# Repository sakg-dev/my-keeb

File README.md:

## My keeb
My first self made mechanical keyboard:
A 60% alice type tactile keyboard, properties:
- Hot swappable: through kailh socker
- 61 keys: no dedicated arrow keys or f keys
- Includes rgb light: individual rgbs

### Imgs:
- Schematics And PCB:
    - Schematics:
        - Main: 
        - Switches: 
        - RGBs: 
    - PCB:
        - F.Cu: 
        - B.Cu: 
        - F.Cu: 
- Onshape:
    - Final:
        - 
        - 

## Development And Output Files
- Layout: [layout_v1.json](/layout/layout_v1.json)
- Schematics and PCB: [kicad/](/kicad/)
- Gerber file: [gerber.zip](/gerber.zip)
- Onshape exports: [onshape_exports/](/onshape_exports/)
- BOM: [BOM.csv](/BOM.csv)
- Onshape Document: [link](https://cad.onshape.com/documents/9aab3062eb3c9d6b80a1ab5a/w/c58e3f2f51a15de1421f10c6/e/e458f6ddd190f7c08079581c)

## BOM
[BOM.csv](/BOM.csv)
| Part                             | Quantity               | Shown Price    | Link                                                                                            |
|----------------------------------|------------------------|----------------|-------------------------------------------------------------------------------------------------|
| PCB                              | 5(minimum site allows) | $40            | JLCPCB - [img](/imgs/pcb.png)                                                                   |
| Raspberry Pi Pico                | 1                      | $4             | https://robu.in/product/raspberry-pi-pico/                                                      |
| 1N4148 Diodes                    | 61                     | $1.5           | https://robu.in/product/1n4148-surface-mount-zener-diode-pack-of-30/                            |
| Capacitor 470uF                  | 1                      |                |                                                                                                 |
| Capacitors 100nF                 | 12                     |                |                                                                                                 |
| Resistor 300 ohm                 | 1                      |                |                                                                                                 |
| SK6812 MINI-E                    | 61                     | $5.5           | https://www.etstore.in/products/e9974?variant=48993209319675                                    |
| GATERON G Pro 3.0 Brown Switches | 75(2 packs - each 35)  | $41            | https://stackskb.com/store/gateron-hotswap-sockets/ - [img](/imgs/switches.png)                 |
| Kailh hot swap socket            | 61                     | $6.3           | https://stackskb.com/store/gateron-hotswap-sockets/                                             |
| Keycaps set                      | 61                     | $79            | [img](/imgs/keycaps.png)                                                                        |
| Stabalizers 2u                   | 4                      | $4.8           | https://www.gateron.com/products/gateron-pcb-mounted-stabilizer?VariantsId=10208                |
| Stabalizer 3u                    | 1                      | $3             | https://shockport.ca/products/cherry-pcb-mount-stabilizers                                      |
| Gasket strip roll                | 1                      | $2.3           | https://www.amazon.in/Aicon-Sponge-Rubber-Adhesive-Insulation/dp/B0DRTJMKD6/                    |
| Heatset insert                   | 6                      | $0.5           | https://onlyscrews.in/products/m2-x-4mm-brass-threaded-inserts                                  |
| Screws                           | 6                      | $0.5           | https://onlyscrews.in/products/m2-x-10mm-phillips-round-head-laptop-screw-dia-2mm-length-10mm   |
| Usb Cable                        | 1                      | $2.7           | https://robu.in/product/5v-3a-usb-to-micro-usb-power-cable-with-led-indicator-for-raspberry-3b/ |
| 3d printed Case and Plate        | 1                      | Not calculated |                                                                                                 |
| Total                            |                        | $193           |                                                                                                 |

## Journal
See [JOURNAL.md](/JOURNAL.md)

## AI usage
Used ai to know more about how a mechanical keyboard works under the hood, measurements i should use, design inspiration, component links and what would be best for me

## Story
It started 2 mnths ago in the beginning of august, i was kinda new in vim and wanted to become a complete keyboard guy and then i saw the YSWS in hackclub named keeb that would fund me if i make the keyboard, at the beginning, i had no idea how tf a mechanical keyboard works but slowly got to know all things and built a keyboard yay. I can have built it in ~2 weeks had i not had my exams and other projects

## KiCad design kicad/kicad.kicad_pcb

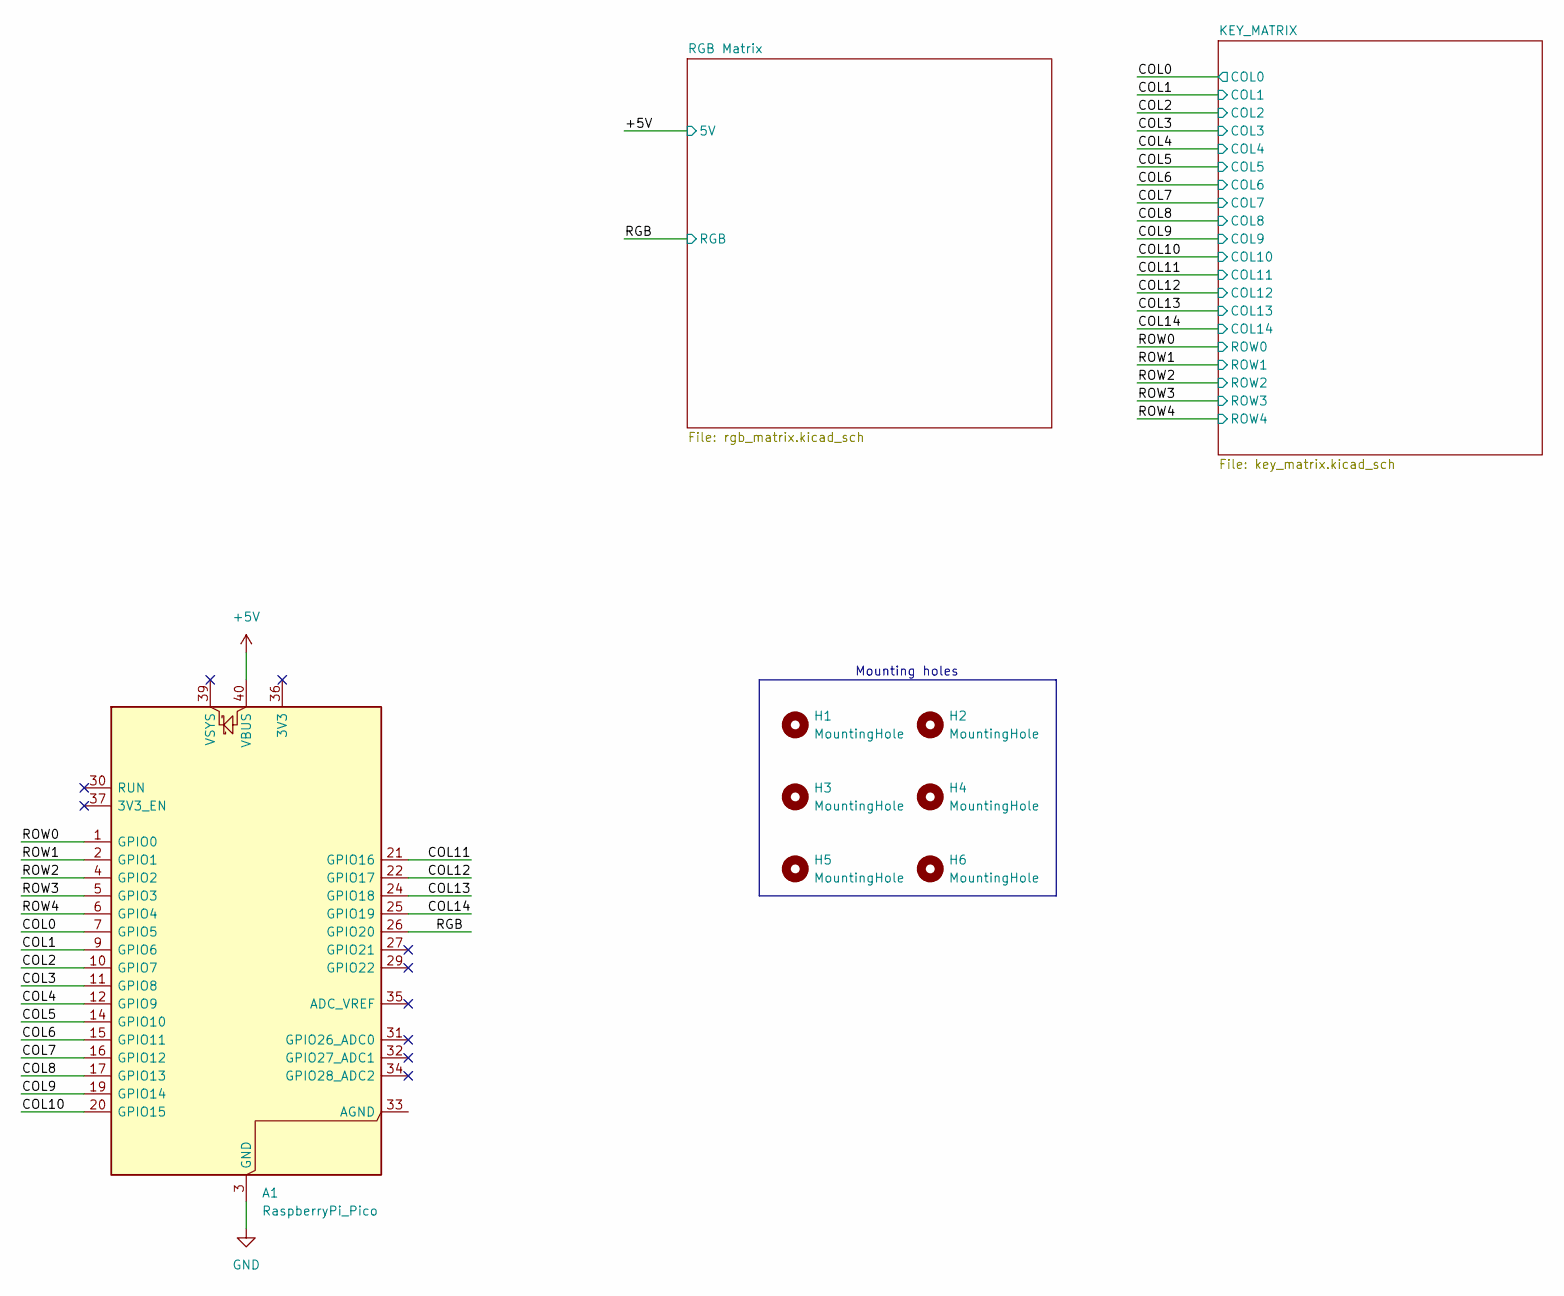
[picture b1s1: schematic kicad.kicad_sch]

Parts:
A1: RaspberryPi_Pico; RaspberryPi_Pico_Common_THT
H1, H2, H3, H4, H5, H6: MountingHole; MountingHole_3.2mm_M3

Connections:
+5V: A1.40 (VBUS); also elsewhere on the board
/COL0: A1.7 (GPIO5); also elsewhere on the board
/COL1: A1.9 (GPIO6); also elsewhere on the board
/COL2: A1.10 (GPIO7); also elsewhere on the board
/COL3: A1.11 (GPIO8); also elsewhere on the board
/COL4: A1.12 (GPIO9); also elsewhere on the board
/COL5: A1.14 (GPIO10); also elsewhere on the board
/COL6: A1.15 (GPIO11); also elsewhere on the board
/COL7: A1.16 (GPIO12); also elsewhere on the board
/COL8: A1.17 (GPIO13); also elsewhere on the board
/COL9: A1.19 (GPIO14); also elsewhere on the board
/COL10: A1.20 (GPIO15); also elsewhere on the board
/COL11: A1.21 (GPIO16); also elsewhere on the board
/COL12: A1.22 (GPIO17); also elsewhere on the board
/COL13: A1.24 (GPIO18); also elsewhere on the board
/COL14: A1.25 (GPIO19); also elsewhere on the board
/RGB: A1.26 (GPIO20); also elsewhere on the board
/ROW0: A1.1 (GPIO0); also elsewhere on the board
/ROW1: A1.2 (GPIO1); also elsewhere on the board
/ROW2: A1.4 (GPIO2); also elsewhere on the board
/ROW3: A1.5 (GPIO3); also elsewhere on the board
/ROW4: A1.6 (GPIO4); also elsewhere on the board
GND: A1.3 (GND), A1.8 (GND), A1.13 (GND), A1.18 (GND), A1.23 (GND), A1.28 (GND), A1.38 (GND); also elsewhere on the board

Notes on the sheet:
Mounting holes

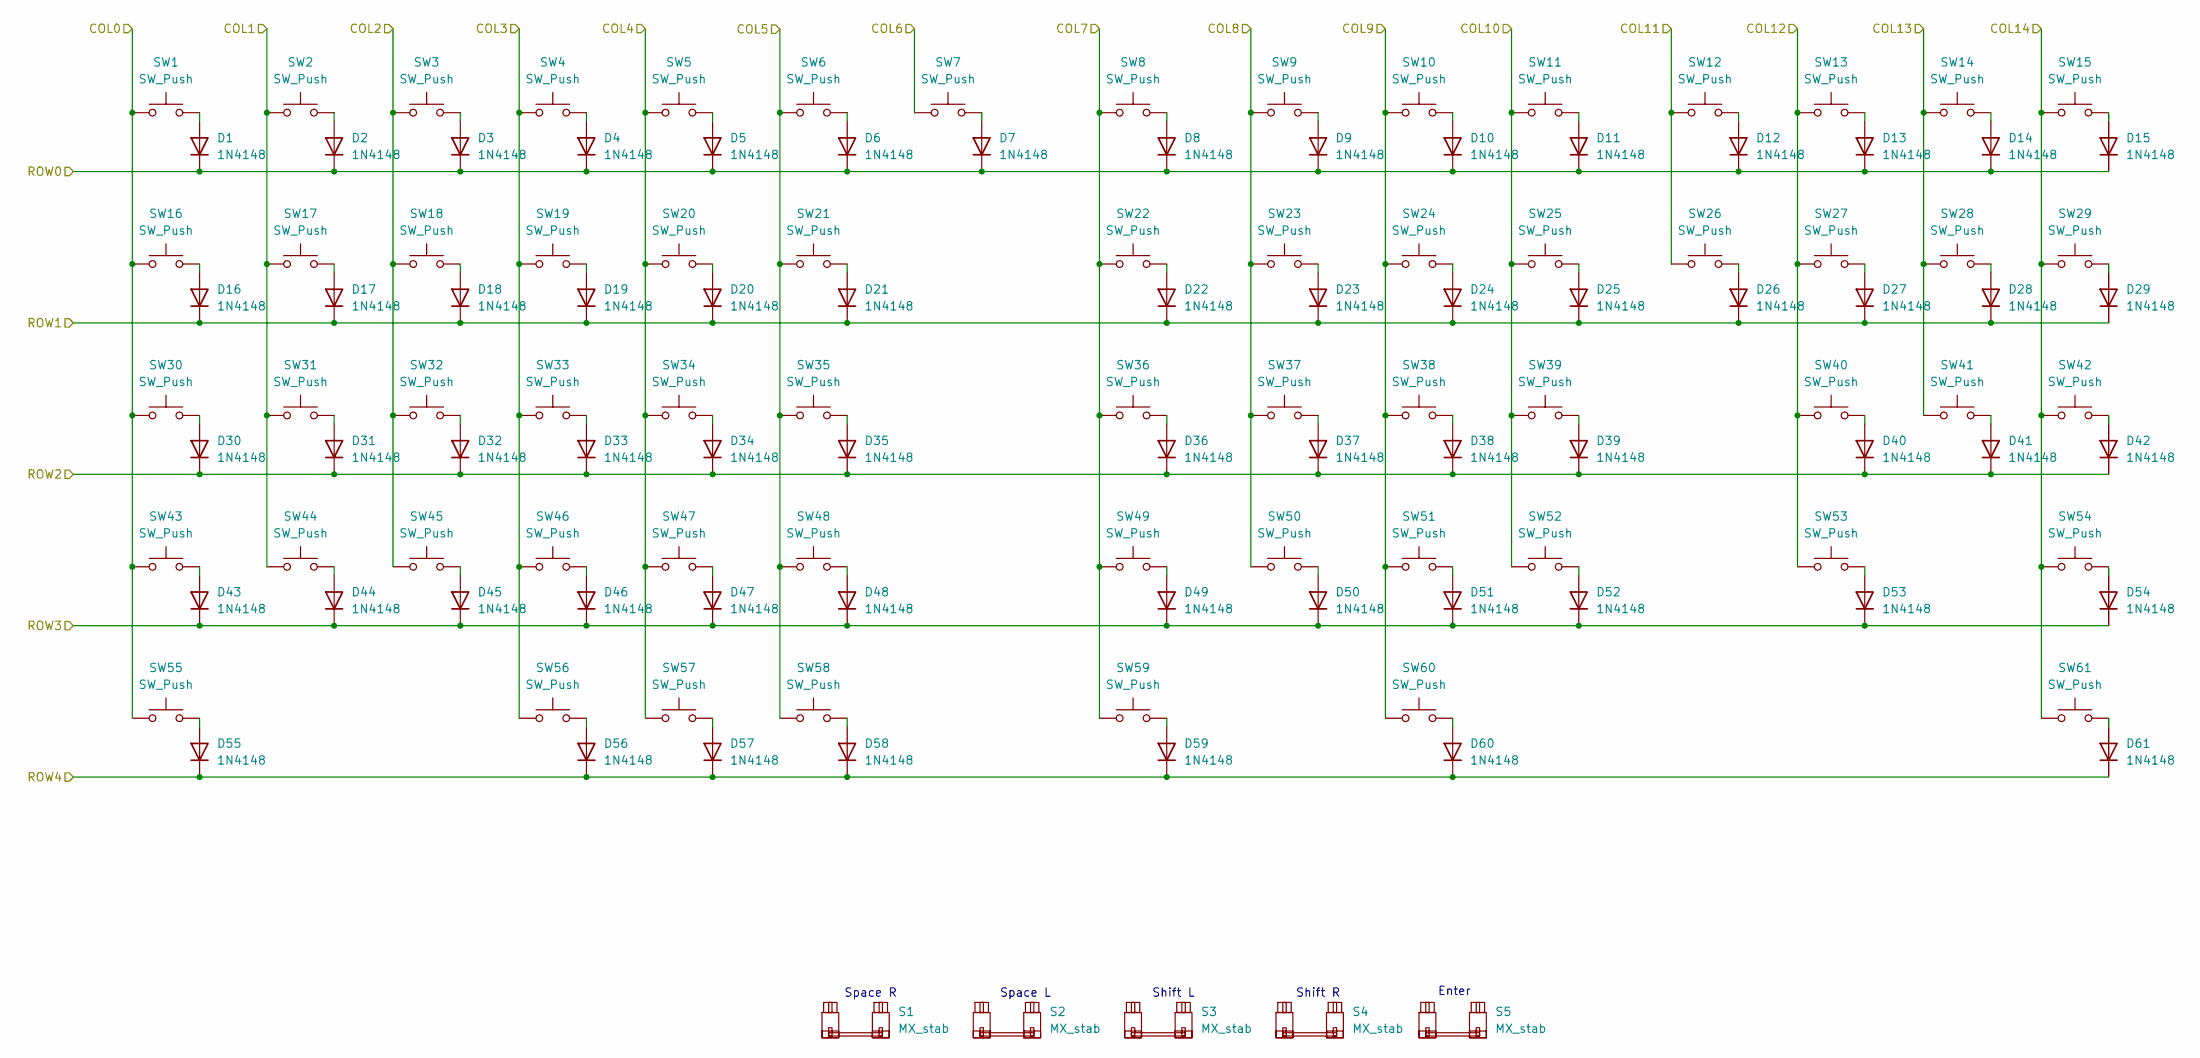
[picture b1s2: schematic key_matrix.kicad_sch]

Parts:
D1, D2, D3, D4, D5, D6, D7, D8, D9, D10, D11, D12, D13, D14, D15, D16, D17, D18, D19, D20, D21, D22, D23, D24, D25, D26, D27, D28, D29, D30, D31, D32, D33, D34, D35, D36, D37, D38, D39, D40, D41, D42, D43, D44, D45, D46, D47, D48, D49, D50, D51, D52, D53, D54, D55, D56, D57, D58, D59, D60, D61: 1N4148; D_DO-35_SOD27_P7.62mm_Horizontal
S1: MX_stab; STAB_MX_3u
S2: MX_stab; STAB_MX_2u
S3, S4, S5: MX_stab; STAB_MX_2.25u
SW1, SW2, SW3, SW4, SW5, SW6, SW7, SW8, SW9, SW10, SW11, SW12, SW13, SW14, SW15, SW16, SW17, SW18, SW19, SW20, SW21, SW22, SW23, SW24, SW25, SW26, SW27, SW28, SW29, SW30, SW31, SW32, SW33, SW34, SW35, SW36, SW37, SW38, SW39, SW40, SW41, SW42, SW43, SW44, SW45, SW46, SW47, SW48, SW49, SW50, SW51, SW52, SW53, SW54, SW55, SW56, SW57, SW58, SW59, SW60, SW61: SW_Push; SW_MX_HS_CPG151101S11_1u

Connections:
/COL0: SW1.1, SW16.1, SW30.1, SW43.1, SW55.1; also elsewhere on the board
/COL1: SW2.1, SW17.1, SW31.1, SW44.1; also elsewhere on the board
/COL2: SW3.1, SW18.1, SW32.1, SW45.1; also elsewhere on the board
/COL3: SW4.1, SW19.1, SW33.1, SW46.1, SW56.1; also elsewhere on the board
/COL4: SW5.1, SW20.1, SW34.1, SW47.1, SW57.1; also elsewhere on the board
/COL5: SW6.1, SW21.1, SW35.1, SW48.1, SW58.1; also elsewhere on the board
/COL6: SW7.1; also elsewhere on the board
/COL7: SW8.1, SW22.1, SW36.1, SW49.1, SW59.1; also elsewhere on the board
/COL8: SW9.1, SW23.1, SW37.1, SW50.1; also elsewhere on the board
/COL9: SW10.1, SW24.1, SW38.1, SW51.1, SW60.1; also elsewhere on the board
/COL10: SW11.1, SW25.1, SW39.1, SW52.1; also elsewhere on the board
/COL11: SW12.1, SW26.1; also elsewhere on the board
/COL12: SW13.1, SW27.1, SW40.1, SW53.1; also elsewhere on the board
/COL13: SW14.1, SW28.1, SW41.1; also elsewhere on the board
/COL14: SW15.1, SW29.1, SW42.1, SW54.1, SW61.1; also elsewhere on the board
/ROW0: D1.1 (K), D2.1 (K), D3.1 (K), D4.1 (K), D5.1 (K), D6.1 (K), D7.1 (K), D8.1 (K), D9.1 (K), D10.1 (K), D11.1 (K), D12.1 (K), D13.1 (K), D14.1 (K), D15.1 (K); also elsewhere on the board
/ROW1: D16.1 (K), D17.1 (K), D18.1 (K), D19.1 (K), D20.1 (K), D21.1 (K), D22.1 (K), D23.1 (K), D24.1 (K), D25.1 (K), D26.1 (K), D27.1 (K), D28.1 (K), D29.1 (K); also elsewhere on the board
/ROW2: D30.1 (K), D31.1 (K), D32.1 (K), D33.1 (K), D34.1 (K), D35.1 (K), D36.1 (K), D37.1 (K), D38.1 (K), D39.1 (K), D40.1 (K), D41.1 (K), D42.1 (K); also elsewhere on the board
/ROW3: D43.1 (K), D44.1 (K), D45.1 (K), D46.1 (K), D47.1 (K), D48.1 (K), D49.1 (K), D50.1 (K), D51.1 (K), D52.1 (K), D53.1 (K), D54.1 (K); also elsewhere on the board
/ROW4: D55.1 (K), D56.1 (K), D57.1 (K), D58.1 (K), D59.1 (K), D60.1 (K), D61.1 (K); also elsewhere on the board
unnamed: D1.2 (A), SW1.2
unnamed: D2.2 (A), SW2.2
unnamed: D3.2 (A), SW3.2
unnamed: D4.2 (A), SW4.2
unnamed: D5.2 (A), SW5.2
unnamed: D6.2 (A), SW6.2
unnamed: D7.2 (A), SW7.2
unnamed: D8.2 (A), SW8.2
unnamed: D9.2 (A), SW9.2
unnamed: D10.2 (A), SW10.2
unnamed: D11.2 (A), SW11.2
unnamed: D12.2 (A), SW12.2
unnamed: D13.2 (A), SW13.2
unnamed: D14.2 (A), SW14.2
unnamed: D15.2 (A), SW15.2
unnamed: D16.2 (A), SW16.2
unnamed: D17.2 (A), SW17.2
unnamed: D18.2 (A), SW18.2
unnamed: D19.2 (A), SW19.2
unnamed: D20.2 (A), SW20.2
unnamed: D21.2 (A), SW21.2
unnamed: D22.2 (A), SW22.2
unnamed: D23.2 (A), SW23.2
unnamed: D24.2 (A), SW24.2
unnamed: D25.2 (A), SW25.2
unnamed: D26.2 (A), SW26.2
unnamed: D27.2 (A), SW27.2
unnamed: D28.2 (A), SW28.2
unnamed: D29.2 (A), SW29.2
unnamed: D30.2 (A), SW30.2
unnamed: D31.2 (A), SW31.2
unnamed: D32.2 (A), SW32.2
unnamed: D33.2 (A), SW33.2
unnamed: D34.2 (A), SW34.2
unnamed: D35.2 (A), SW35.2
unnamed: D36.2 (A), SW36.2
unnamed: D37.2 (A), SW37.2
unnamed: D38.2 (A), SW38.2
unnamed: D39.2 (A), SW39.2
unnamed: D40.2 (A), SW40.2
unnamed: D41.2 (A), SW41.2
unnamed: D42.2 (A), SW42.2
unnamed: D43.2 (A), SW43.2
unnamed: D44.2 (A), SW44.2
unnamed: D45.2 (A), SW45.2
unnamed: D46.2 (A), SW46.2
unnamed: D47.2 (A), SW47.2
unnamed: D48.2 (A), SW48.2
unnamed: D49.2 (A), SW49.2
unnamed: D50.2 (A), SW50.2
unnamed: D51.2 (A), SW51.2
unnamed: D52.2 (A), SW52.2
unnamed: D53.2 (A), SW53.2
unnamed: D54.2 (A), SW54.2
unnamed: D55.2 (A), SW55.2
unnamed: D56.2 (A), SW56.2
unnamed: D57.2 (A), SW57.2
unnamed: D58.2 (A), SW58.2
unnamed: D59.2 (A), SW59.2
unnamed: D60.2 (A), SW60.2
unnamed: D61.2 (A), SW61.2

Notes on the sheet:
Shift R
Enter
Shift L
Space L
Space R

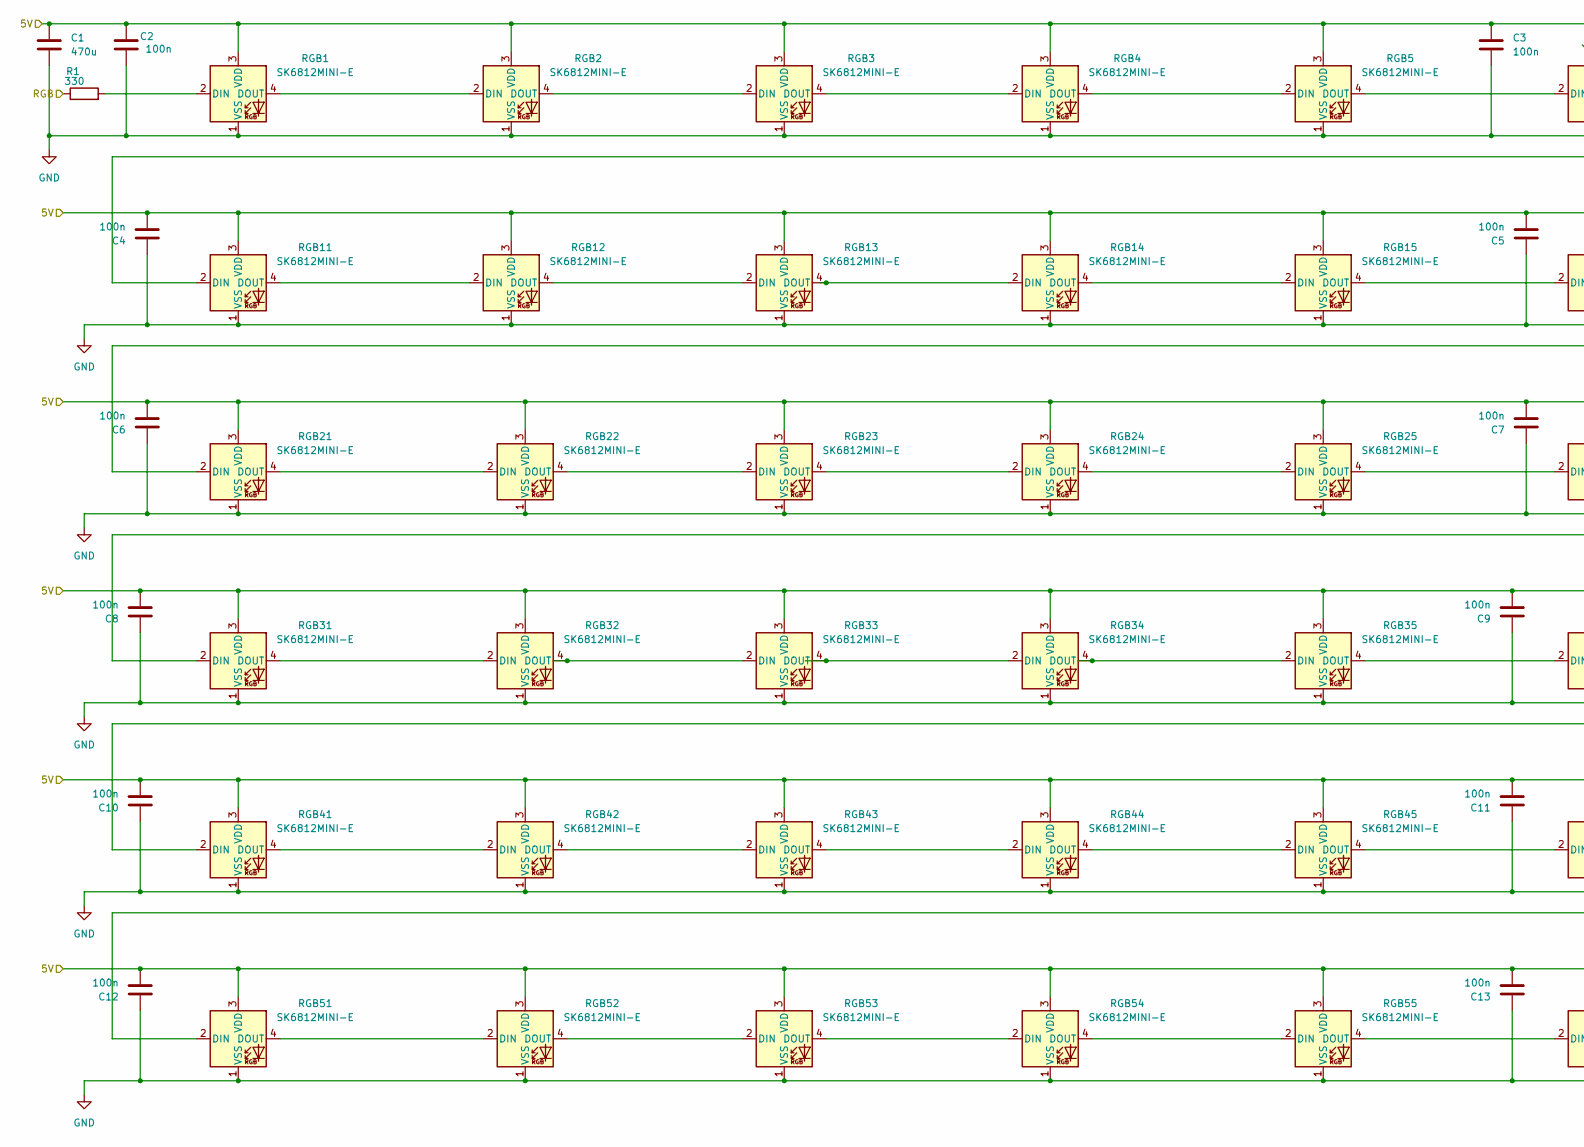
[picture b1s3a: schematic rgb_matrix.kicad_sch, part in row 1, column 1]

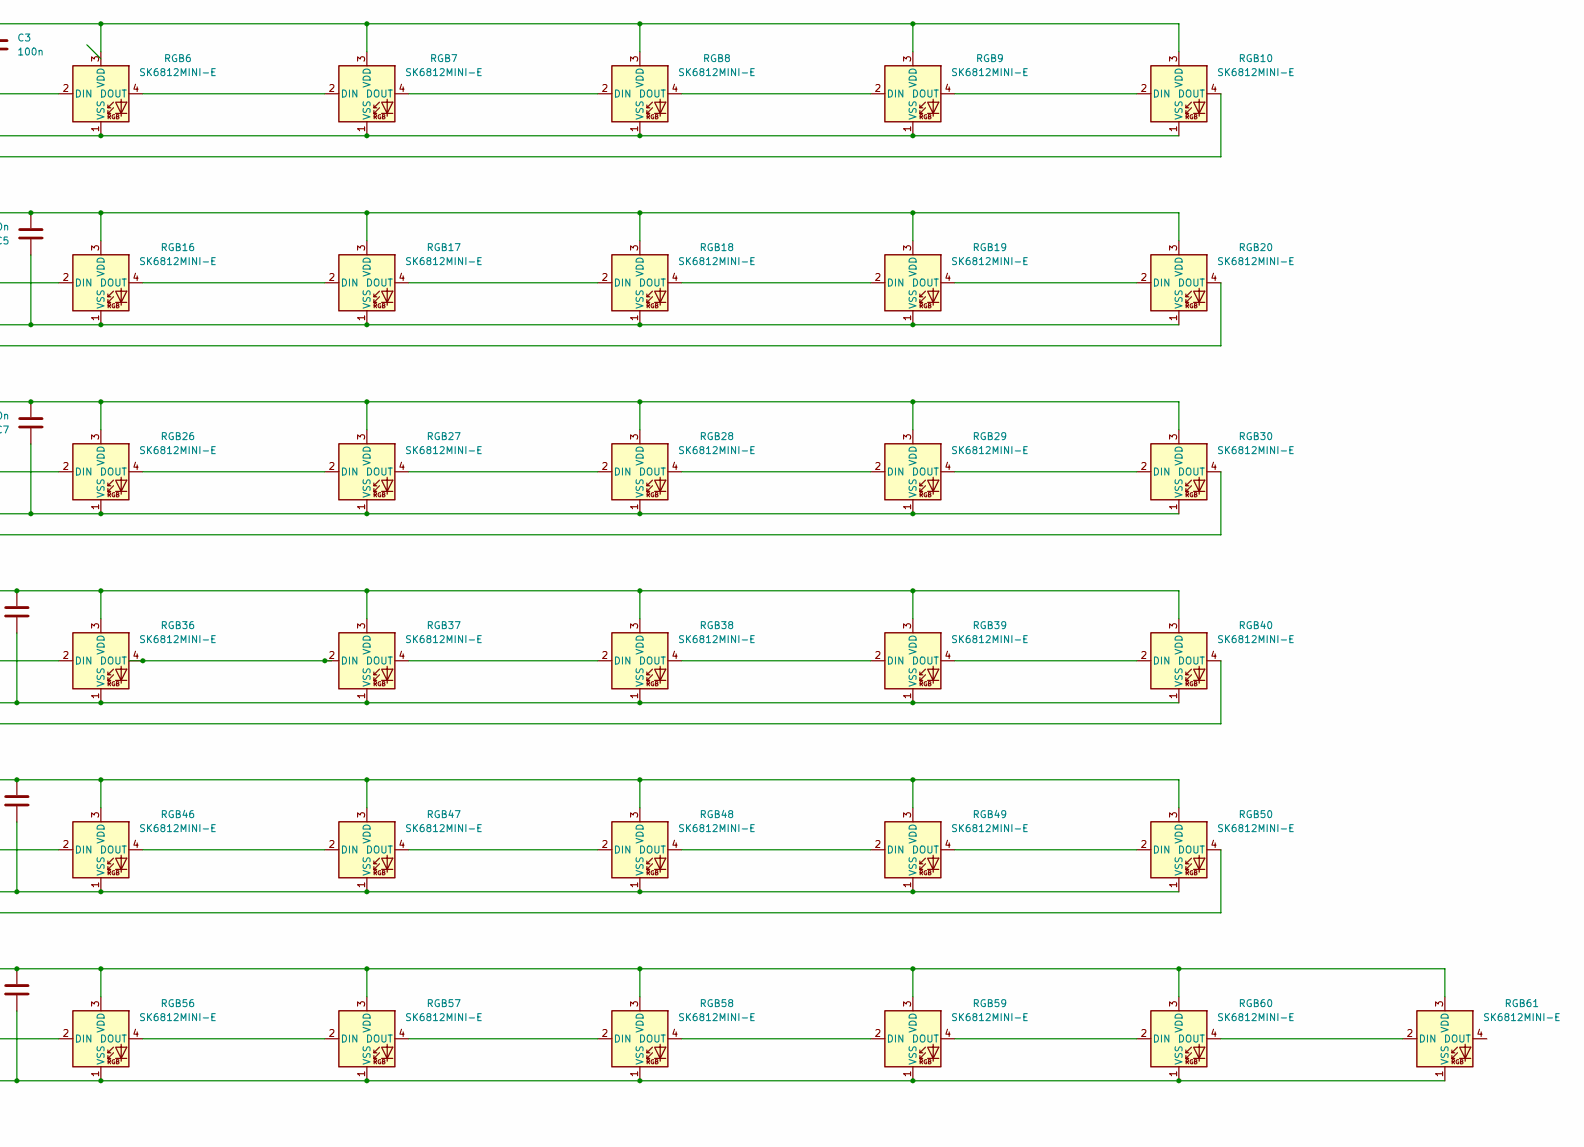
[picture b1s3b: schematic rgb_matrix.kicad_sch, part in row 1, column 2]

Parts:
C1: 470u; CP_EIA-7343-31_Kemet-D_HandSolder
C2, C3, C4, C5, C6, C7, C8, C9, C10, C11, C12, C13: 100n; C_0603_1608Metric_Pad1.08x0.95mm_HandSolder
R1: 330; R_0603_1608Metric_Pad0.98x0.95mm_HandSolder
RGB1, RGB2, RGB3, RGB4, RGB5, RGB6, RGB7, RGB8, RGB9, RGB10, RGB11, RGB12, RGB13, RGB14, RGB15, RGB16, RGB17, RGB18, RGB19, RGB20, RGB21, RGB22, RGB23, RGB24, RGB25, RGB26, RGB27, RGB28, RGB29, RGB30, RGB31, RGB32, RGB33, RGB34, RGB35, RGB36, RGB37, RGB38, RGB39, RGB40, RGB41, RGB42, RGB43, RGB44, RGB45, RGB46, RGB47, RGB48, RGB49, RGB50, RGB51, RGB52, RGB53, RGB54, RGB55, RGB56, RGB57, RGB58, RGB59, RGB60, RGB61: SK6812MINI-E; LED_SK6812MINI-E_3.2x2.8mm_P1.5mm_ReverseMount

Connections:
+5V: C1.1, C2.2, C3.1, C4.2, C5.2, C6.2, C7.2, C8.2, C9.2, C10.2, C11.2, C12.2, C13.2, RGB1.3 (VDD), RGB2.3 (VDD), RGB3.3 (VDD), RGB4.3 (VDD), RGB5.3 (VDD), RGB6.3 (VDD), RGB7.3 (VDD), RGB8.3 (VDD), RGB9.3 (VDD), RGB10.3 (VDD), RGB11.3 (VDD), RGB12.3 (VDD), RGB13.3 (VDD), RGB14.3 (VDD), RGB15.3 (VDD), RGB16.3 (VDD), RGB17.3 (VDD), RGB18.3 (VDD), RGB19.3 (VDD), RGB20.3 (VDD), RGB21.3 (VDD), RGB22.3 (VDD), RGB23.3 (VDD), RGB24.3 (VDD), RGB25.3 (VDD), RGB26.3 (VDD), RGB27.3 (VDD), RGB28.3 (VDD), RGB29.3 (VDD), RGB30.3 (VDD), RGB31.3 (VDD), RGB32.3 (VDD), RGB33.3 (VDD), RGB34.3 (VDD), RGB35.3 (VDD), RGB36.3 (VDD), RGB37.3 (VDD), RGB38.3 (VDD), RGB39.3 (VDD), RGB40.3 (VDD), RGB41.3 (VDD), RGB42.3 (VDD), RGB43.3 (VDD), RGB44.3 (VDD), RGB45.3 (VDD), RGB46.3 (VDD), RGB47.3 (VDD), RGB48.3 (VDD), RGB49.3 (VDD), RGB50.3 (VDD), RGB51.3 (VDD), RGB52.3 (VDD), RGB53.3 (VDD), RGB54.3 (VDD), RGB55.3 (VDD), RGB56.3 (VDD), RGB57.3 (VDD), RGB58.3 (VDD), RGB59.3 (VDD), RGB60.3 (VDD), RGB61.3 (VDD); also elsewhere on the board
/RGB: R1.1; also elsewhere on the board
GND: C1.2, C2.1, C3.2, C4.1, C5.1, C6.1, C7.1, C8.1, C9.1, C10.1, C11.1, C12.1, C13.1, RGB1.1 (VSS), RGB2.1 (VSS), RGB3.1 (VSS), RGB4.1 (VSS), RGB5.1 (VSS), RGB6.1 (VSS), RGB7.1 (VSS), RGB8.1 (VSS), RGB9.1 (VSS), RGB10.1 (VSS), RGB11.1 (VSS), RGB12.1 (VSS), RGB13.1 (VSS), RGB14.1 (VSS), RGB15.1 (VSS), RGB16.1 (VSS), RGB17.1 (VSS), RGB18.1 (VSS), RGB19.1 (VSS), RGB20.1 (VSS), RGB21.1 (VSS), RGB22.1 (VSS), RGB23.1 (VSS), RGB24.1 (VSS), RGB25.1 (VSS), RGB26.1 (VSS), RGB27.1 (VSS), RGB28.1 (VSS), RGB29.1 (VSS), RGB30.1 (VSS), RGB31.1 (VSS), RGB32.1 (VSS), RGB33.1 (VSS), RGB34.1 (VSS), RGB35.1 (VSS), RGB36.1 (VSS), RGB37.1 (VSS), RGB38.1 (VSS), RGB39.1 (VSS), RGB40.1 (VSS), RGB41.1 (VSS), RGB42.1 (VSS), RGB43.1 (VSS), RGB44.1 (VSS), RGB45.1 (VSS), RGB46.1 (VSS), RGB47.1 (VSS), RGB48.1 (VSS), RGB49.1 (VSS), RGB50.1 (VSS), RGB51.1 (VSS), RGB52.1 (VSS), RGB53.1 (VSS), RGB54.1 (VSS), RGB55.1 (VSS), RGB56.1 (VSS), RGB57.1 (VSS), RGB58.1 (VSS), RGB59.1 (VSS), RGB60.1 (VSS), RGB61.1 (VSS); also elsewhere on the board
unnamed: R1.2, RGB1.2 (DIN)
unnamed: RGB1.4 (DOUT), RGB2.2 (DIN)
unnamed: RGB2.4 (DOUT), RGB3.2 (DIN)
unnamed: RGB3.4 (DOUT), RGB4.2 (DIN)
unnamed: RGB4.4 (DOUT), RGB5.2 (DIN)
unnamed: RGB5.4 (DOUT), RGB6.2 (DIN)
unnamed: RGB6.4 (DOUT), RGB7.2 (DIN)
unnamed: RGB7.4 (DOUT), RGB8.2 (DIN)
unnamed: RGB8.4 (DOUT), RGB9.2 (DIN)
unnamed: RGB9.4 (DOUT), RGB10.2 (DIN)
unnamed: RGB10.4 (DOUT), RGB11.2 (DIN)
unnamed: RGB11.4 (DOUT), RGB12.2 (DIN)
unnamed: RGB12.4 (DOUT), RGB13.2 (DIN)
unnamed: RGB13.4 (DOUT), RGB14.2 (DIN)
unnamed: RGB14.4 (DOUT), RGB15.2 (DIN)
unnamed: RGB15.4 (DOUT), RGB16.2 (DIN)
unnamed: RGB16.4 (DOUT), RGB17.2 (DIN)
unnamed: RGB17.4 (DOUT), RGB18.2 (DIN)
unnamed: RGB18.4 (DOUT), RGB19.2 (DIN)
unnamed: RGB19.4 (DOUT), RGB20.2 (DIN)
unnamed: RGB20.4 (DOUT), RGB21.2 (DIN)
unnamed: RGB21.4 (DOUT), RGB22.2 (DIN)
unnamed: RGB22.4 (DOUT), RGB23.2 (DIN)
unnamed: RGB23.4 (DOUT), RGB24.2 (DIN)
unnamed: RGB24.4 (DOUT), RGB25.2 (DIN)
unnamed: RGB25.4 (DOUT), RGB26.2 (DIN)
unnamed: RGB26.4 (DOUT), RGB27.2 (DIN)
unnamed: RGB27.4 (DOUT), RGB28.2 (DIN)
unnamed: RGB28.4 (DOUT), RGB29.2 (DIN)
unnamed: RGB29.4 (DOUT), RGB30.2 (DIN)
unnamed: RGB30.4 (DOUT), RGB31.2 (DIN)
unnamed: RGB31.4 (DOUT), RGB32.2 (DIN)
unnamed: RGB32.4 (DOUT), RGB33.2 (DIN)
unnamed: RGB33.4 (DOUT), RGB34.2 (DIN)
unnamed: RGB34.4 (DOUT), RGB35.2 (DIN)
unnamed: RGB35.4 (DOUT), RGB36.2 (DIN)
unnamed: RGB36.4 (DOUT), RGB37.2 (DIN)
unnamed: RGB37.4 (DOUT), RGB38.2 (DIN)
unnamed: RGB38.4 (DOUT), RGB39.2 (DIN)
unnamed: RGB39.4 (DOUT), RGB40.2 (DIN)
unnamed: RGB40.4 (DOUT), RGB41.2 (DIN)
unnamed: RGB41.4 (DOUT), RGB42.2 (DIN)
unnamed: RGB42.4 (DOUT), RGB43.2 (DIN)
unnamed: RGB43.4 (DOUT), RGB44.2 (DIN)
unnamed: RGB44.4 (DOUT), RGB45.2 (DIN)
unnamed: RGB45.4 (DOUT), RGB46.2 (DIN)
unnamed: RGB46.4 (DOUT), RGB47.2 (DIN)
unnamed: RGB47.4 (DOUT), RGB48.2 (DIN)
unnamed: RGB48.4 (DOUT), RGB49.2 (DIN)
unnamed: RGB49.4 (DOUT), RGB50.2 (DIN)
unnamed: RGB50.4 (DOUT), RGB51.2 (DIN)
unnamed: RGB51.4 (DOUT), RGB52.2 (DIN)
unnamed: RGB52.4 (DOUT), RGB53.2 (DIN)
unnamed: RGB53.4 (DOUT), RGB54.2 (DIN)
unnamed: RGB54.4 (DOUT), RGB55.2 (DIN)
unnamed: RGB55.4 (DOUT), RGB56.2 (DIN)
unnamed: RGB56.4 (DOUT), RGB57.2 (DIN)
unnamed: RGB57.4 (DOUT), RGB58.2 (DIN)
unnamed: RGB58.4 (DOUT), RGB59.2 (DIN)
unnamed: RGB59.4 (DOUT), RGB60.2 (DIN)
unnamed: RGB60.4 (DOUT), RGB61.2 (DIN)

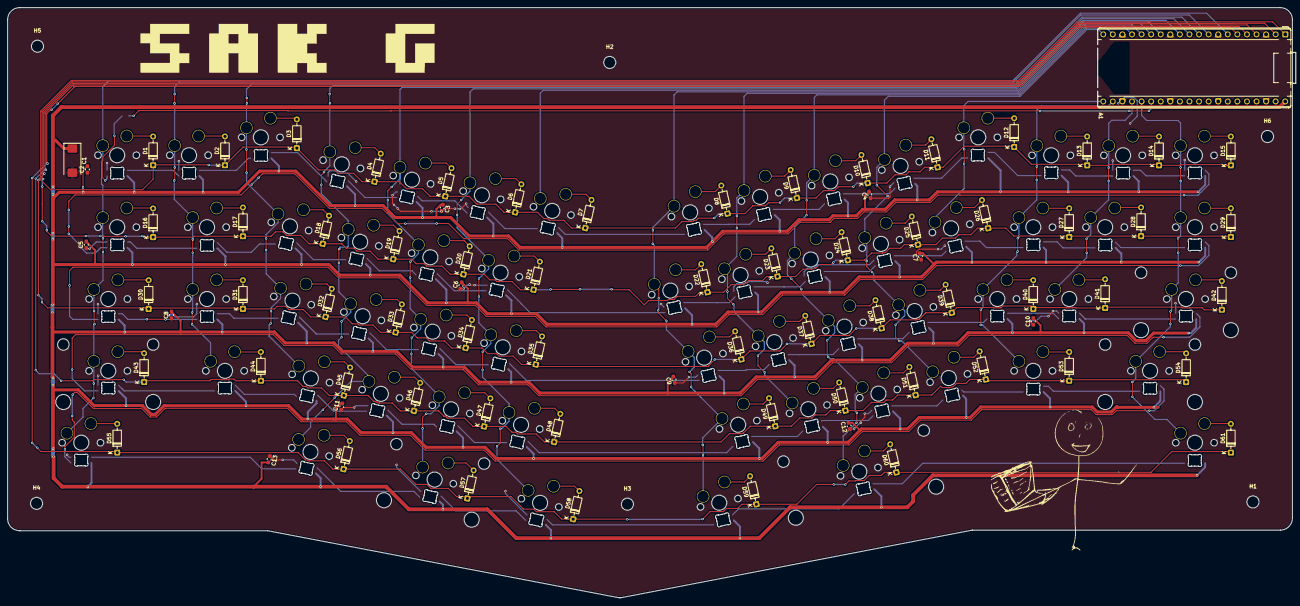
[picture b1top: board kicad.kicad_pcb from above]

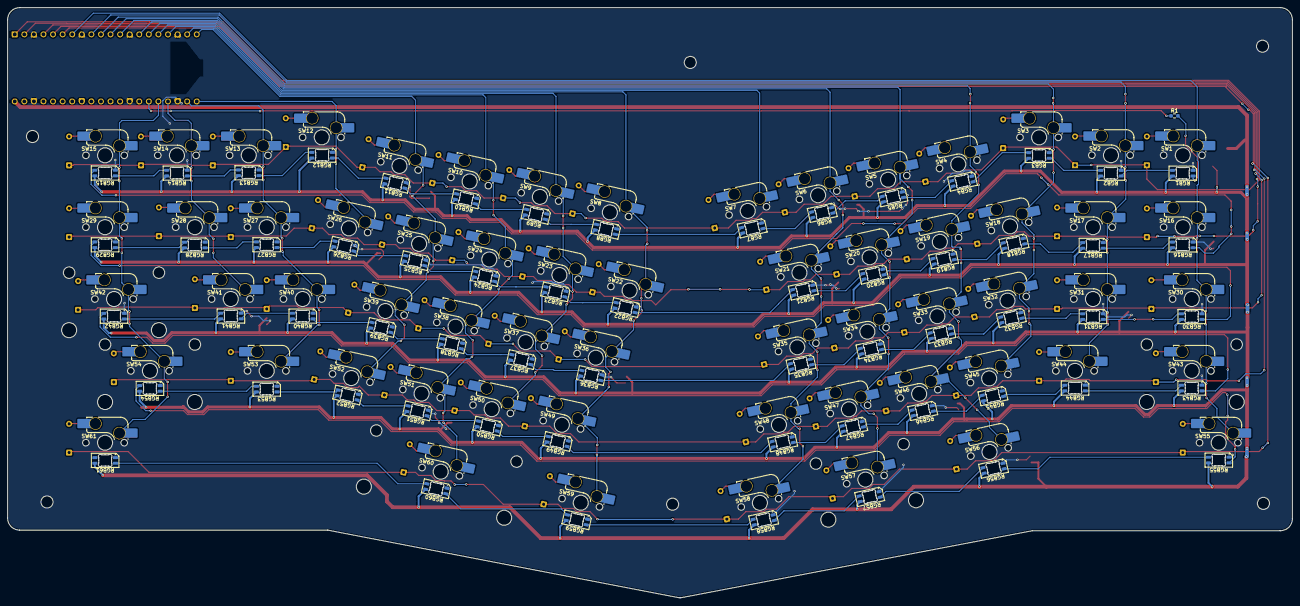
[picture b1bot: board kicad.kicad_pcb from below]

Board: 2 copper layers, 340.6 x 156.5 mm, 209 parts (123 on the bottom side), 145 nets.

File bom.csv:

"Reference","Qty","Value","DNP","Exclude from BOM","Exclude from Board","Exclude from Simulation","Exclude from Position Files","Footprint","Datasheet"
"A1","1","RaspberryPi_Pico","","","","","${EXCLUDE_FROM_POS_FILES}","Module:RaspberryPi_Pico_Common_THT","https://datasheets.raspberrypi.com/pico/pico-datasheet.pdf"
"C1","1","470u","","","","","${EXCLUDE_FROM_POS_FILES}","Capacitor_Tantalum_SMD:CP_EIA-7343-31_Kemet-D_HandSolder",""
"C2,C3,C4,C5,C6,C7,C8,C9,C10,C11,C12,C13","12","100n","","","","","${EXCLUDE_FROM_POS_FILES}","Capacitor_SMD:C_0603_1608Metric_Pad1.08x0.95mm_HandSolder",""
"D1,D2,D3,D4,D5,D6,D7,D8,D9,D10,D11,D12,D13,D14,D15,D16,D17,D18,D19,D20,D21,D22,D23,D24,D25,D26,D27,D28,D29,D30,D31,D32,D33,D34,D35,D36,D37,D38,D39,D40,D41,D42,D43,D44,D45,D46,D47,D48,D49,D50,D51,D52,D53,D54,D55,D56,D57,D58,D59,D60,D61","61","1N4148","","","","","${EXCLUDE_FROM_POS_FILES}","Diode_THT:D_DO-35_SOD27_P7.62mm_Horizontal","https://assets.nexperia.com/documents/data-sheet/1N4148_1N4448.pdf"
"R1","1","330","","","","","${EXCLUDE_FROM_POS_FILES}","Resistor_SMD:R_0603_1608Metric_Pad0.98x0.95mm_HandSolder",""
"RGB1,RGB2,RGB3,RGB4,RGB5,RGB6,RGB7,RGB8,RGB9,RGB10,RGB11,RGB12,RGB13,RGB14,RGB15,RGB16,RGB17,RGB18,RGB19,RGB20,RGB21,RGB22,RGB23,RGB24,RGB25,RGB26,RGB27,RGB28,RGB29,RGB30,RGB31,RGB32,RGB33,RGB34,RGB35,RGB36,RGB37,RGB38,RGB39,RGB40,RGB41,RGB42,RGB43,RGB44,RGB45,RGB46,RGB47,RGB48,RGB49,RGB50,RGB51,RGB52,RGB53,RGB54,RGB55,RGB56,RGB57,RGB58,RGB59,RGB60,RGB61","61","SK6812MINI-E","","","","","${EXCLUDE_FROM_POS_FILES}","LED_SMD:LED_SK6812MINI-E_3.2x2.8mm_P1.5mm_ReverseMount","https://www.lcsc.com/datasheet/C5149201.pdf"
"S1","1","MX_stab","","","","","${EXCLUDE_FROM_POS_FILES}","PCM_marbastlib-mx:STAB_MX_3u",""
"S2","1","MX_stab","","","","","${EXCLUDE_FROM_POS_FILES}","PCM_marbastlib-mx:STAB_MX_2u",""
"S3,S4,S5","3","MX_stab","","","","","${EXCLUDE_FROM_POS_FILES}","PCM_marbastlib-mx:STAB_MX_2.25u",""
"SW1,SW2,SW3,SW4,SW5,SW6,SW7,SW8,SW9,SW10,SW11,SW12,SW13,SW14,SW15,SW16,SW17,SW18,SW19,SW20,SW21,SW22,SW23,SW24,SW25,SW26,SW27,SW28,SW29,SW30,SW31,SW32,SW33,SW34,SW35,SW36,SW37,SW38,SW39,SW40,SW41,SW42,SW43,SW44,SW45,SW46,SW47,SW48,SW49,SW50,SW51,SW52,SW53,SW54,SW55,SW56,SW57,SW58,SW59,SW60,SW61","61","SW_Push","","","","","${EXCLUDE_FROM_POS_FILES}","PCM_marbastlib-mx:SW_MX_HS_CPG151101S11_1u",""
